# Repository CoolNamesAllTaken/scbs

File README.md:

# scbs
Single Cell Battery Simulator for testing a BMS.

# CELLSIM 4S

Cellsim 4S is a low-current battery pack simulator that simulates four battery cells in series. Each cell has a settable output voltage between 2.5-4.5V and a readable output current. Communication is done over a 9600 baud UART link using a custom serial protocol.

[DATASHEET](word/datasheet_cellsim_4s-1.0.0.pdf)

# SCBS Pico

SCBS Pico is a single battery cell simulator that can be daisy chained with other devices of the same type in order to build a full simulated battery pack. It is the basic building block of the CELLSIM 4S.

[DATASHEET](word/datasheet_scbs_pico.pdf)

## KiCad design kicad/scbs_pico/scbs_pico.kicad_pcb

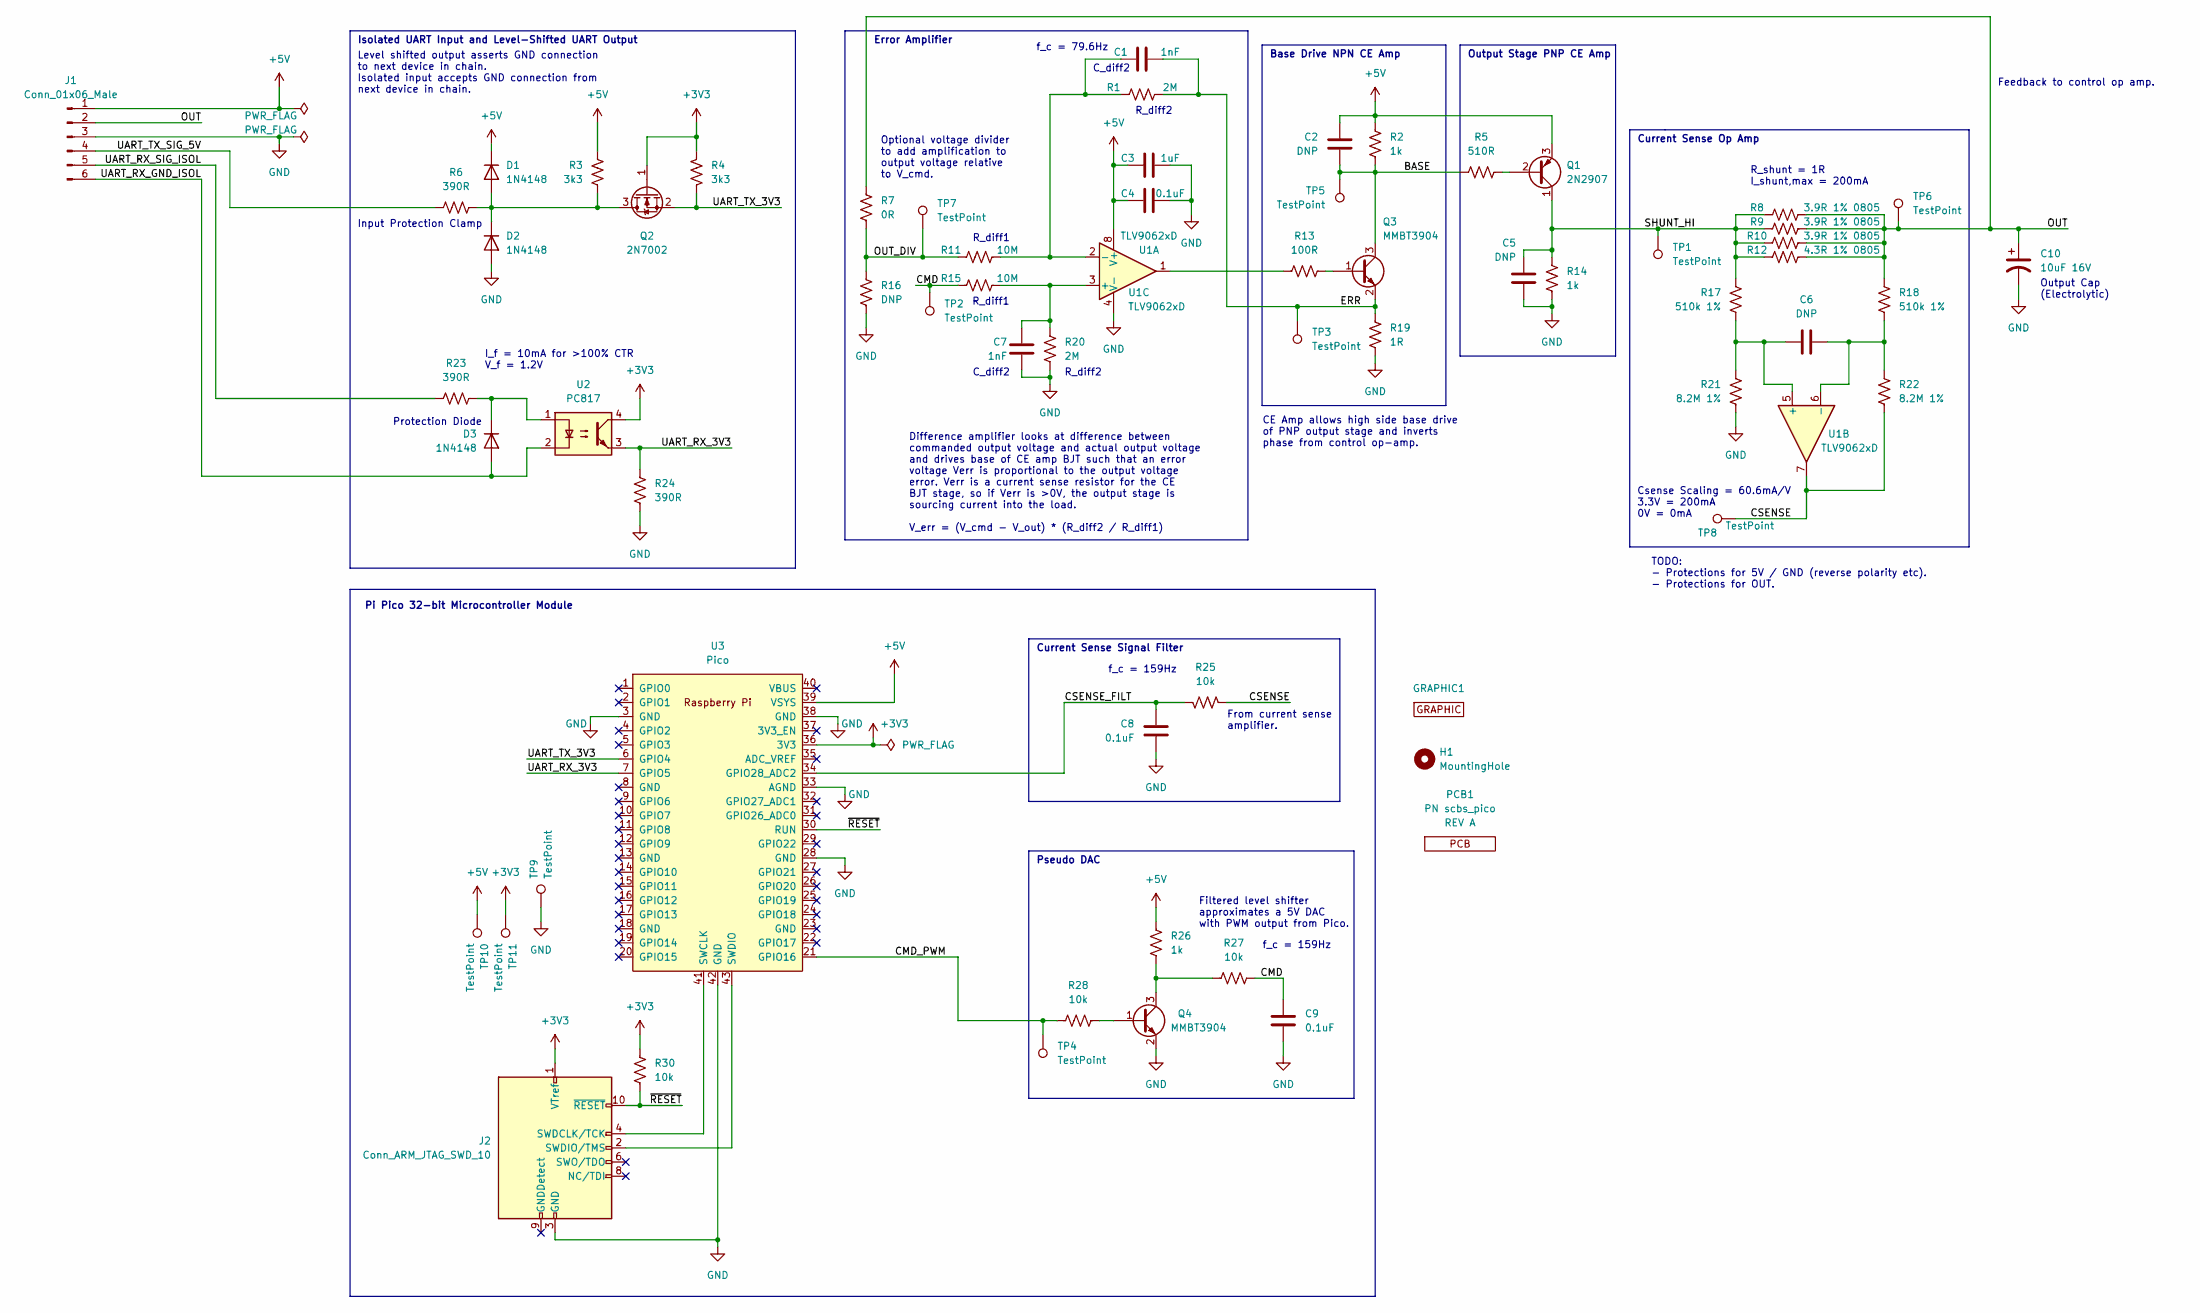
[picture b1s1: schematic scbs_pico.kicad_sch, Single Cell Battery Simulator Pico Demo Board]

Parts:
C1, C7: 1nF; C_0805_2012Metric
C2, C5, C6: DNP; C_0805_2012Metric
C3: 1uF; C_0805_2012Metric
C4, C8, C9: 0.1uF; C_0805_2012Metric
C10: 10uF 16V
D1, D2, D3: 1N4148; D_SOD-123; MPN 1N4148W-TP
GRAPHIC1: Graphic; bird_with_pants_small_flipped; MPN DNP
H1: MountingHole; MountingHole_3.2mm_M3; MPN DNP
J1: Conn_01x06_Male; PinHeader_1x06_P2.54mm_Horizontal; MPN PREC006SBAN-M71RC
J2: Conn_ARM_JTAG_SWD_10; PinHeader_2x05_P1.27mm_Vertical_SMD; MPN 4048
PCB1: PCB; PCB_PN_REV_small; MPN PN scbs_pico
Q1: 2N2907; TO-92; MPN PN2907ATF
Q2: 2N7002; SOT-23; MPN 2N7002
Q3, Q4: MMBT3904; SOT-23
R1, R20: 2M; R_0805_2012Metric
R2, R14, R26: 1k; R_0805_2012Metric
R3, R4: 3k3; R_0805_2012Metric
R5: 510R; R_0805_2012Metric
R6, R23, R24: 390R; R_0805_2012Metric
R7: 0R; R_0805_2012Metric
R8, R9, R10: 3.9R 1% 0805; R_0805_2012Metric
R11, R15: 10M; R_0805_2012Metric
R12: 4.3R 1% 0805; R_0805_2012Metric
R13: 100R; R_0805_2012Metric
R16: DNP; R_0805_2012Metric
R17, R18: 510k 1%; R_0805_2012Metric
R19: 1R; R_0805_2012Metric
R21, R22: 8.2M 1%; R_0805_2012Metric
R25, R27, R28, R30: 10k; R_0805_2012Metric
TP1, TP2, TP3, TP4, TP5, TP6, TP7, TP8, TP9, TP10, TP11: TestPoint; TestPoint_Pad_2.0x2.0mm
U1: TLV9062xD; SOIC-8_3.9x4.9mm_P1.27mm; MPN TLV9062IDR
U2: PC817; DIP-4_W7.62mm; MPN BPC-817S ( C BIN )
U3: Pico; RPi_Pico_SMD_TH; MPN SC0915

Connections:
+3V3: J2.1 (VTref), Q2.1 (G), R4.1, R30.1, TP11.1, U2.4, U3.36 (3V3)
+5V: C2.1, C3.1, C4.1, D1.1 (K), J1.1, Q1.3 (E), R2.1, R3.1, R26.1, TP10.1, U1.8 (V+), U3.39 (VSYS)
/BASE: C2.2, Q3.3 (C), R2.2, R5.1, TP5.1
/CMD: C9.1, R15.1, R27.2, TP2.1
/CMD_PWM: R28.1, TP4.1, U3.21 (GPIO16)
/CSENSE: R22.2, R25.1, TP8.1, U1.7
/CSENSE_FILT: C8.1, R25.2, U3.34 (GPIO28_ADC2)
/ERR: C1.2, Q3.2 (E), R1.2, R19.1, TP3.1
/OUT: C10.1, J1.2, R7.1, R8.2, R9.2, R10.2, R12.2, R18.1, TP6.1
/OUT_DIV: R7.2, R11.1, R16.1, TP7.1
/SHUNT_HI: C5.1, Q1.1 (C), R8.1, R9.1, R10.1, R12.1, R14.1, R17.1, TP1.1
/UART_RX_3V3: R24.1, U2.3, U3.7 (GPIO5)
/UART_RX_GND_ISOL: D3.2 (A), J1.6, U2.2
/UART_RX_SIG_ISOL: J1.5, R23.1
/UART_TX_3V3: Q2.2 (S), R4.2, U3.6 (GPIO4)
/UART_TX_SIG_5V: J1.4, R6.1
/~RESET: J2.10 (~RESET), R30.2, U3.30 (RUN)
GND: C3.2, C4.2, C5.2, C7.2, C8.2, C9.2, C10.2, D2.2 (A), J1.3, J2.3 (GND), J2.5 (GND), Q4.2 (E), R14.2, R16.2, R19.2, R20.2, R21.2, R24.2, TP9.1, U1.4 (V-), U3.3 (GND), U3.28 (GND), U3.33 (AGND), U3.38 (GND), U3.42 (GND)
unnamed: C1.1, R1.1, R11.2, U1.2 (-)
unnamed: C6.1, R17.2, R21.1, U1.5 (+)
unnamed: C6.2, R18.2, R22.1, U1.6 (-)
unnamed: C7.1, R15.2, R20.1, U1.3 (+)
unnamed: D1.2 (A), D2.1 (K), Q2.3 (D), R3.2, R6.2
unnamed: D3.1 (K), R23.2, U2.1
unnamed: J2.2 (SWDIO/TMS), U3.43 (SWDIO)
unnamed: J2.4 (SWDCLK/TCK), U3.41 (SWCLK)
unnamed: Q1.2 (B), R5.2
unnamed: Q3.1 (B), R13.2
unnamed: Q4.1 (B), R28.2
unnamed: Q4.3 (C), R26.2, R27.1
unnamed: R13.1, U1.1

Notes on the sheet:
R_diff1
Input Protection Clamp
Difference amplifier looks at difference between commanded output voltage and actual output voltage and drives base of CE amp BJT such that an error voltage Verr is proportional to the output voltage error. Verr is a current sense resistor for the CE BJT stage, so if Verr is >0V, the output stage i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
Protection Diode
Error Amplifier
Pseudo DAC
f_c = 79.6Hz
f_c = 159Hz
Csense Scaling = 60.6mA/V 3.3V = 200mA 0V = 0mA
Current Sense Op Amp
C_diff2
Feedback to control op amp.
Isolated UART Input and Level-Shifted UART Output
Pi Pico 32-bit Microcontroller Module
Optional voltage divider to add amplification to output voltage relative to V_cmd.
Output Stage PNP CE Amp
R_diff2
From current sense amplifier.
CE Amp allows high side base drive of PNP output stage and inverts phase from control op-amp.
Filtered level shifter approximates a 5V DAC with PWM output from Pico.
TODO: - Protections for 5V / GND (reverse polarity etc). - Protections for OUT.
Base Drive NPN CE Amp
R_shunt = 1R I_shunt,max = 200mA
Output Cap (Electrolytic)
I_f = 10mA for >100% CTR V_f = 1.2V
Current Sense Signal Filter
Level shifted output asserts GND connection to next device in chain. Isolated input accepts GND connection from next device in chain.

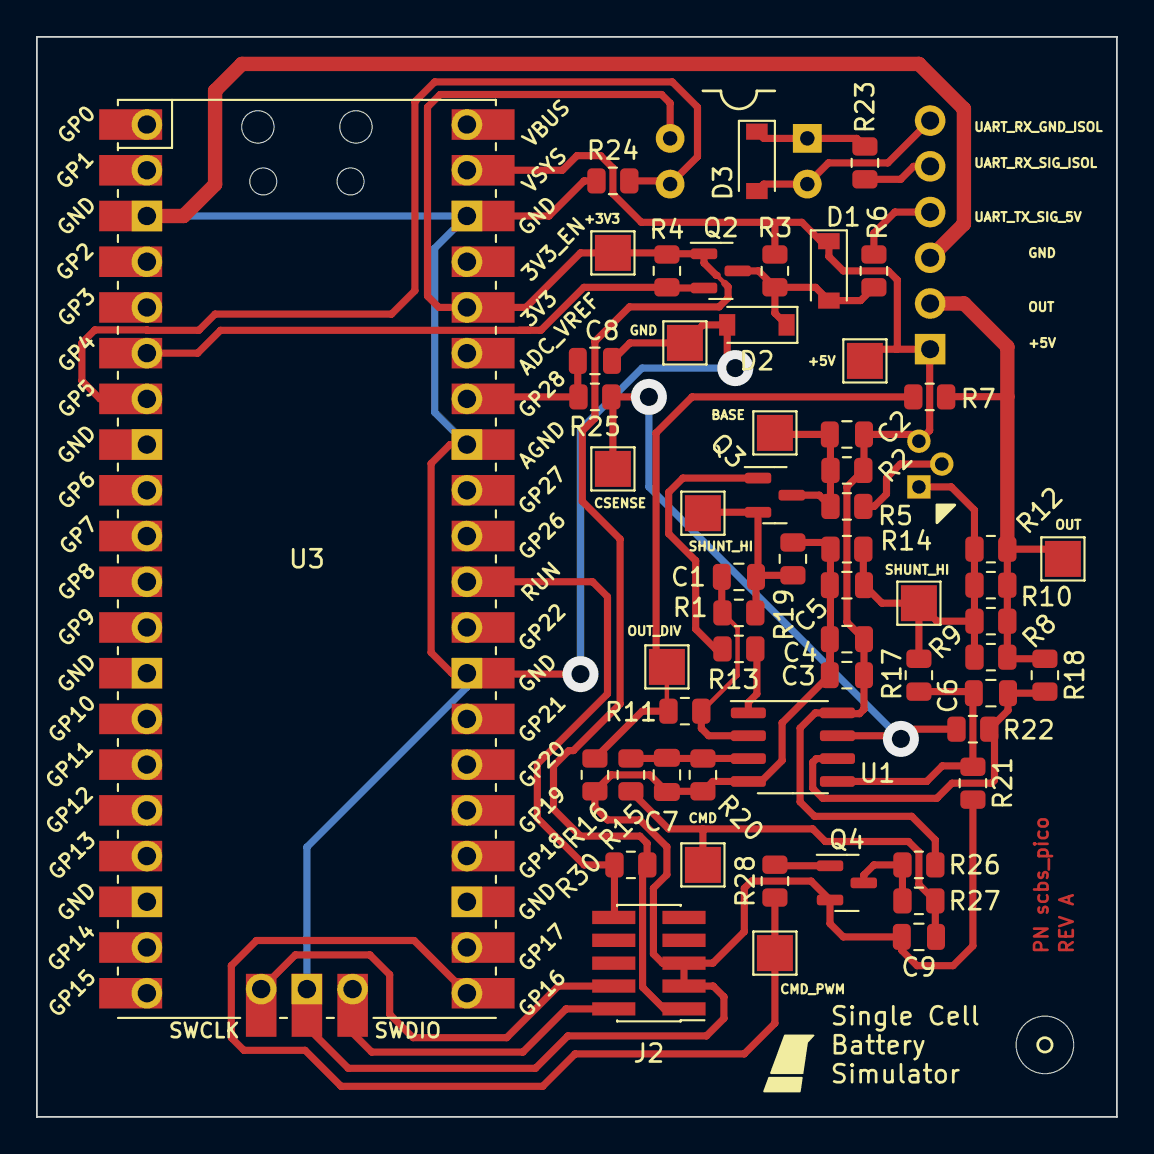
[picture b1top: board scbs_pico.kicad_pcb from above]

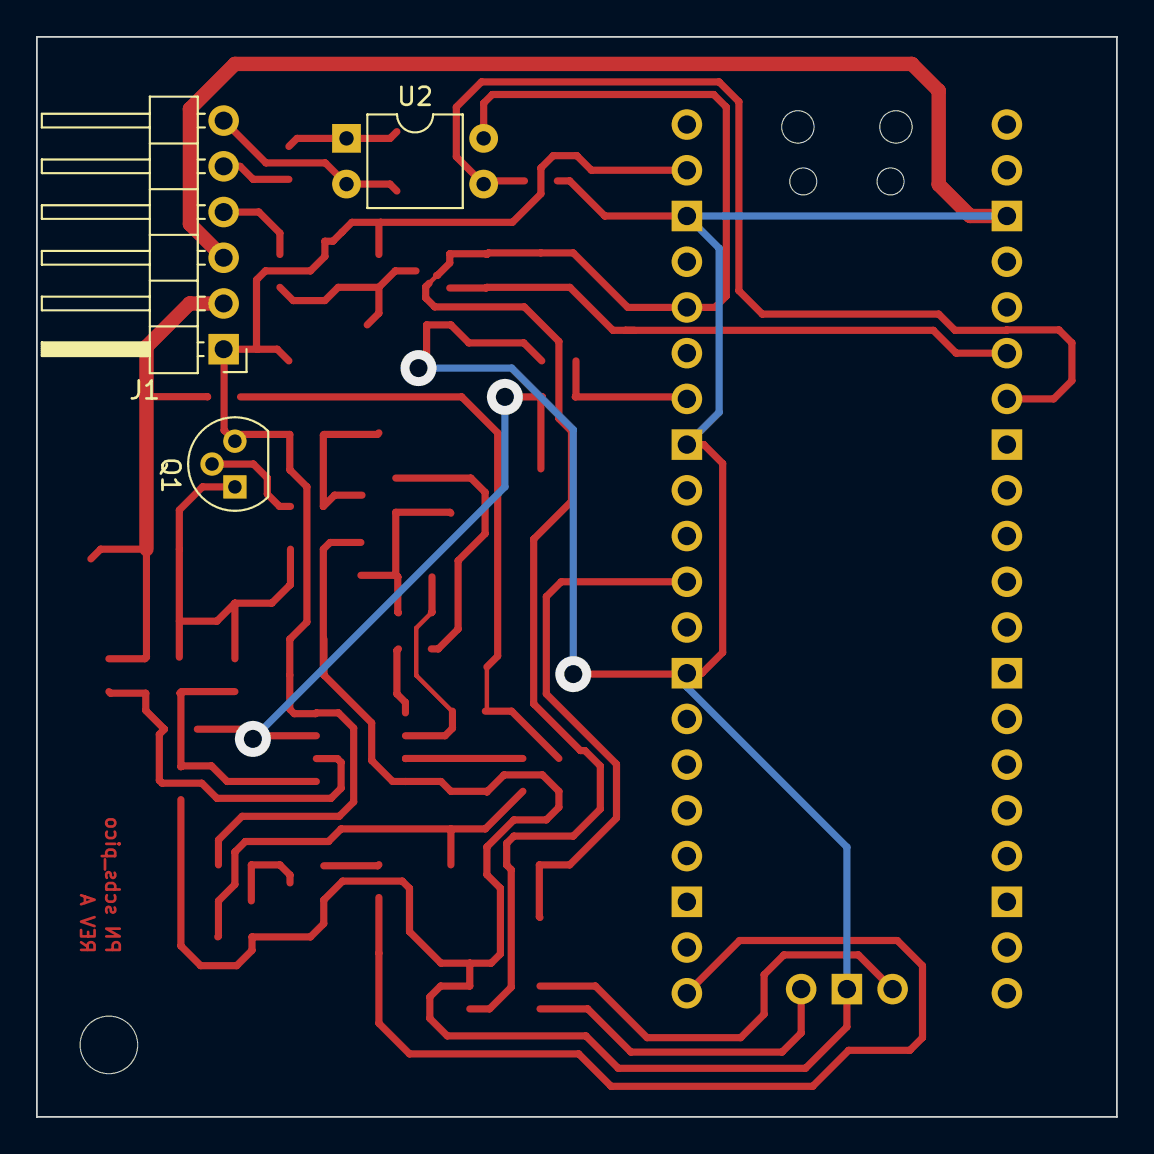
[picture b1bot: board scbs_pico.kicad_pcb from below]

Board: 2 copper layers, 60.0 x 60.0 mm, 64 parts (3 on the bottom side), 31 nets.

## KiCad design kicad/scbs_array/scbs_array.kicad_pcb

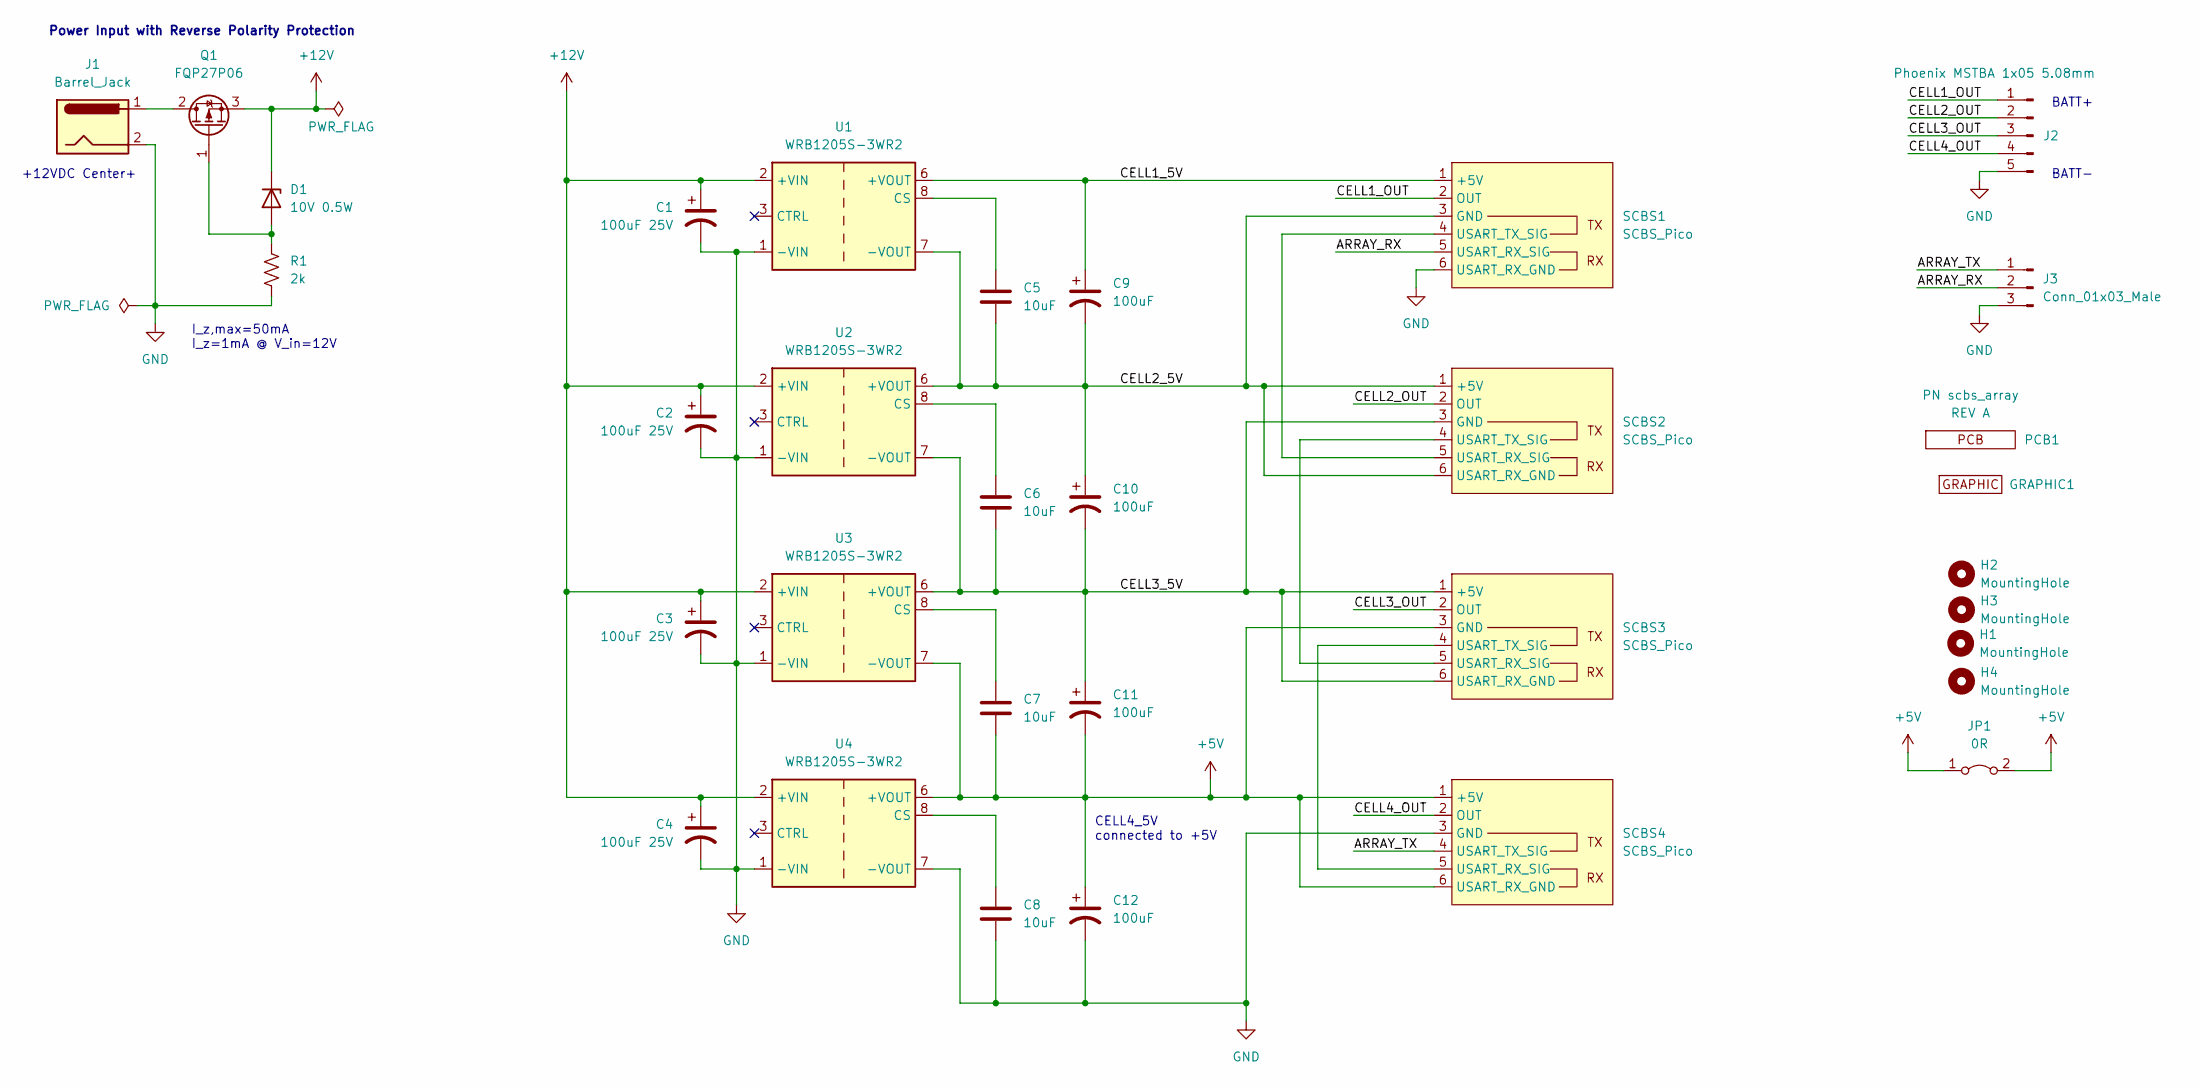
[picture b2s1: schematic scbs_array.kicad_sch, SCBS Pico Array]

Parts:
C1, C2, C3, C4: 100uF 25V; CP_Radial_D5.0mm_P2.50mm
C5, C6, C7, C8: 10uF; C_0805_2012Metric
C9, C10, C11, C12: 100uF; CP_Radial_D5.0mm_P2.50mm
D1: 10V 0.5W; D_MELF
GRAPHIC1: Graphic; bird_with_pants_small_flipped
H1, H2, H3, H4: MountingHole; MountingHole_3.2mm_M3
J1: Barrel_Jack; SOFNG_DC005-T20; MPN DC005-T20
J2: Phoenix MSTBA 1x05 5.08mm; PhoenixContact_MSTBA_2,5_5-G-5,08_1x05_P5.08mm_Horizontal
J3: Conn_01x03_Male; PinHeader_1x03_P2.54mm_Horizontal
JP1: 0R; R_0805_2012Metric
PCB1: PCB; PCB_PN_REV; MPN PN scbs_array
Q1: FQP27P06; TO-220-3_Horizontal_TabDown; MPN FQP27P06
R1: 2k; R_0805_2012Metric
SCBS1, SCBS2, SCBS3, SCBS4: SCBS_Pico
U1, U2, U3, U4: WRB1205S-3WR2; Converter_DCDC_TRACO_TMR-xxxx_THT

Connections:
+5V: C7.2, C11.2, C12.1, JP1.1 (A), JP1.2 (B), SCBS3.3 (GND), SCBS4.1 (+5V), SCBS4.6 (USART_RX_GND), U3.7 (-VOUT), U4.6 (+VOUT)
+12V: C1.1, C2.1, C3.1, C4.1, D1.1 (K), Q1.3 (S), U1.2 (+VIN), U2.2 (+VIN), U3.2 (+VIN), U4.2 (+VIN)
/ARRAY_RX: J3.2, SCBS1.5 (USART_RX_SIG)
/ARRAY_TX: J3.1, SCBS4.4 (USART_TX_SIG)
/CELL1_5V: C9.1, SCBS1.1 (+5V), U1.6 (+VOUT)
/CELL1_OUT: J2.1, SCBS1.2 (OUT)
/CELL2_5V: C5.2, C9.2, C10.1, SCBS1.3 (GND), SCBS2.1 (+5V), SCBS2.6 (USART_RX_GND), U1.7 (-VOUT), U2.6 (+VOUT)
/CELL2_OUT: J2.2, SCBS2.2 (OUT)
/CELL3_5V: C6.2, C10.2, C11.1, SCBS2.3 (GND), SCBS3.1 (+5V), SCBS3.6 (USART_RX_GND), U2.7 (-VOUT), U3.6 (+VOUT)
/CELL3_OUT: J2.3, SCBS3.2 (OUT)
/CELL4_OUT: J2.4, SCBS4.2 (OUT)
GND: C1.2, C2.2, C3.2, C4.2, C8.2, C12.2, J1.2, J2.5, J3.3, R1.2, SCBS1.6 (USART_RX_GND), SCBS4.3 (GND), U1.1 (-VIN), U2.1 (-VIN), U3.1 (-VIN), U4.1 (-VIN), U4.7 (-VOUT)
unnamed: C5.1, U1.8 (CS)
unnamed: C6.1, U2.8 (CS)
unnamed: C7.1, U3.8 (CS)
unnamed: C8.1, U4.8 (CS)
unnamed: D1.2 (A), Q1.1 (G), R1.1
unnamed: J1.1, Q1.2 (D)
unnamed: SCBS1.4 (USART_TX_SIG), SCBS2.5 (USART_RX_SIG)
unnamed: SCBS2.4 (USART_TX_SIG), SCBS3.5 (USART_RX_SIG)
unnamed: SCBS3.4 (USART_TX_SIG), SCBS4.5 (USART_RX_SIG)

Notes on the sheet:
+12VDC Center+
CELL4_5V connected to +5V
I_z,max=50mA I_z=1mA @ V_in=12V
Power Input with Reverse Polarity Protection
BATT-
BATT+

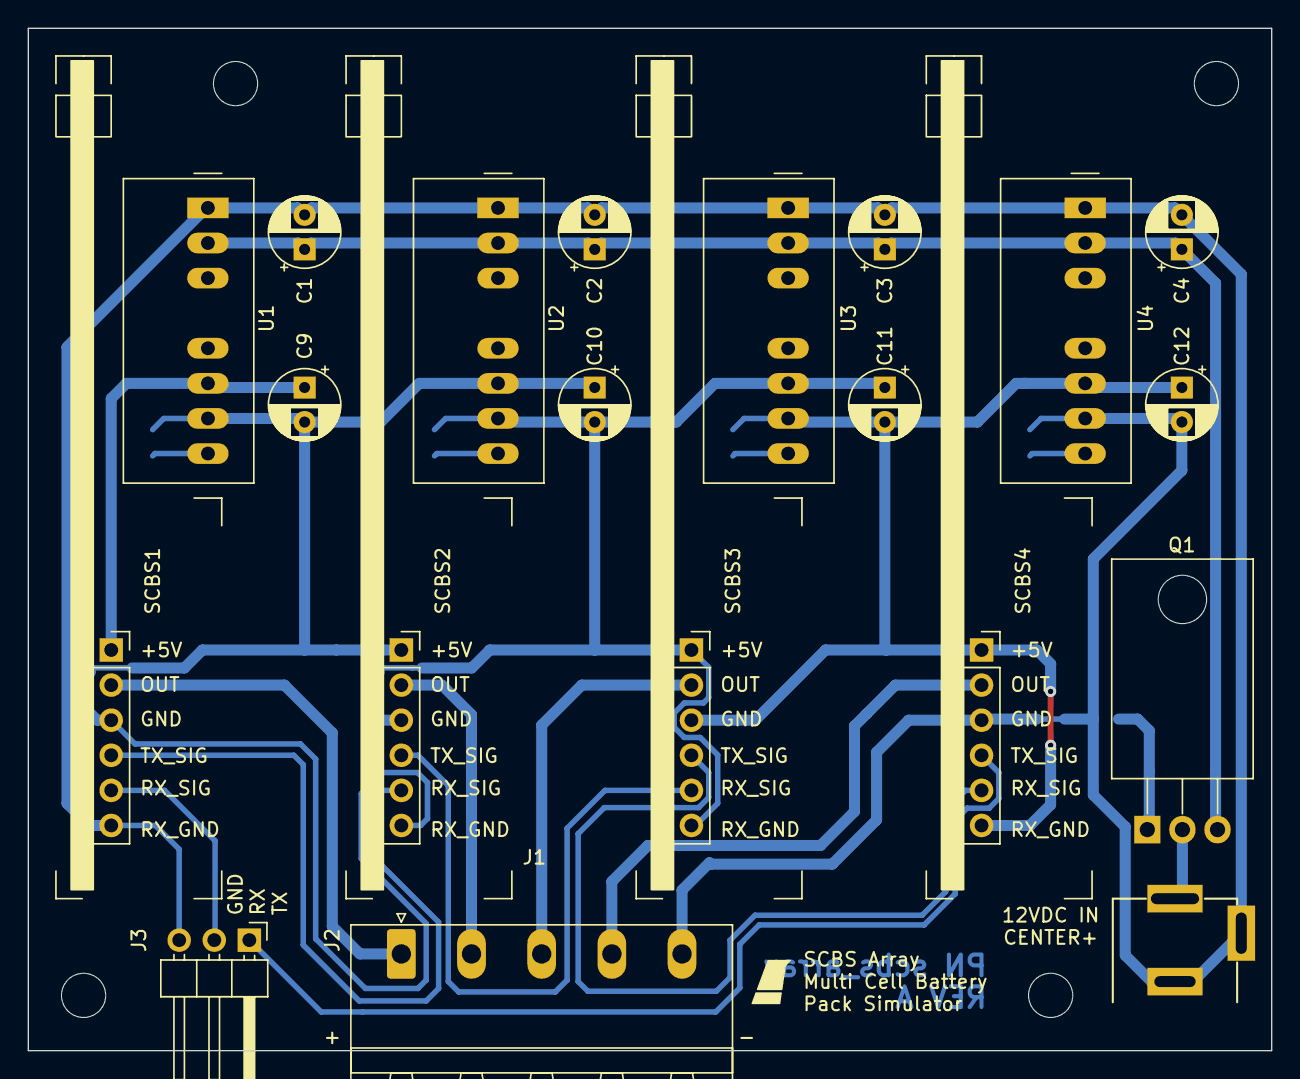
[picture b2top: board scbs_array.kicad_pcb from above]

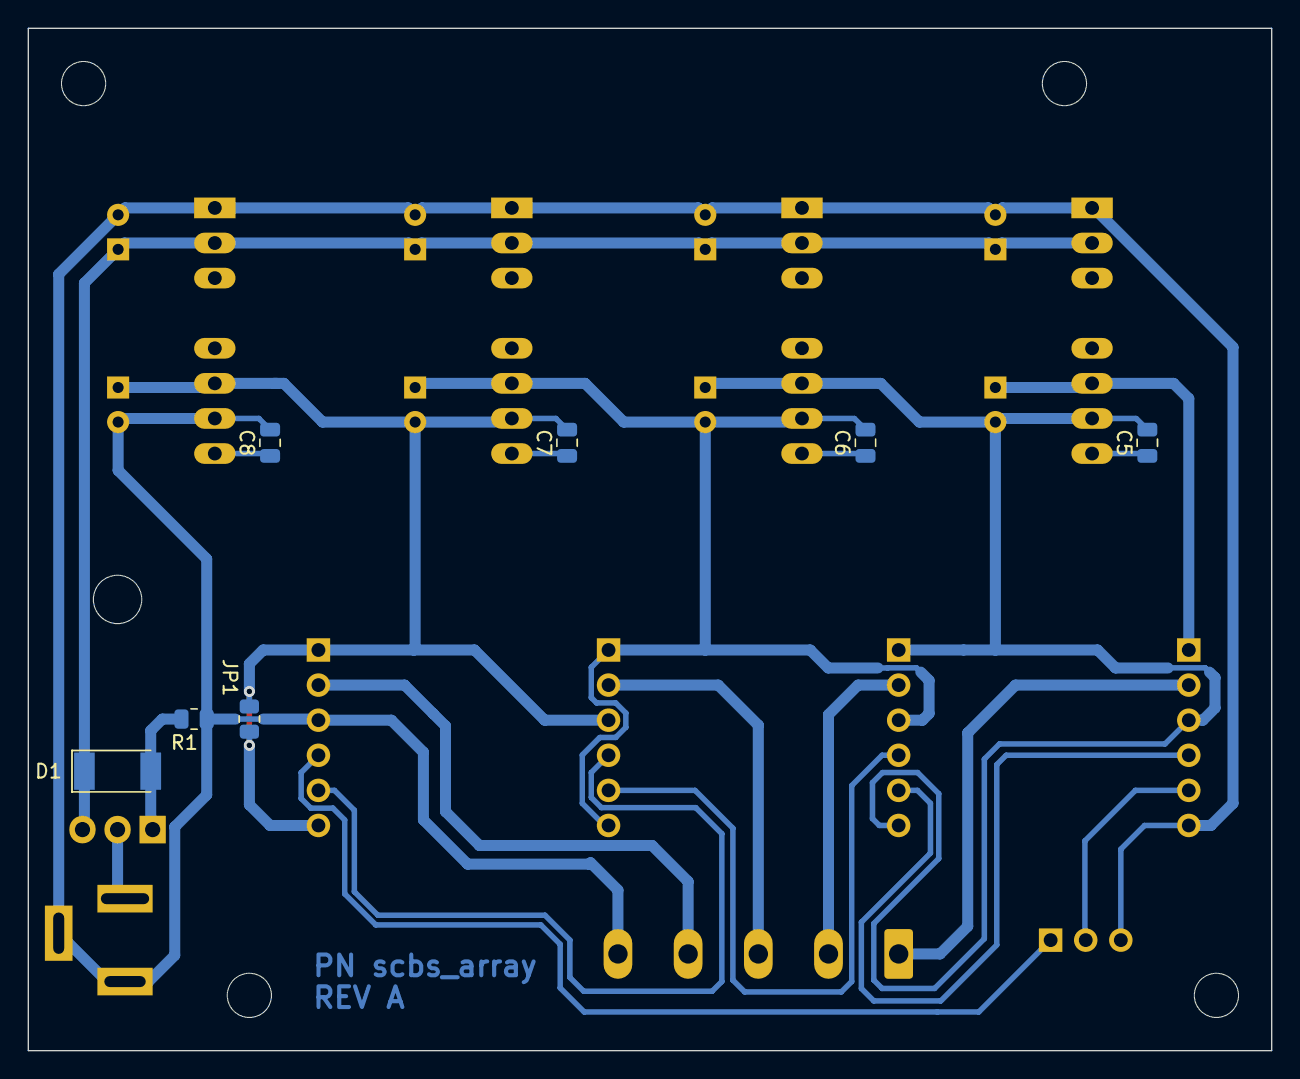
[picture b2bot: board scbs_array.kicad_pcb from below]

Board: 2 copper layers, 90.0 x 74.0 mm, 33 parts (8 on the bottom side), 21 nets.

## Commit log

2022-11-06 Demo board v0.1
2022-11-08 scbs_pico hardware Rev A, initial firmware
2022-11-12 Saving progress of unsuccessful mock attempt
2022-11-12 Add unit tested MRD packet type
2022-11-12 Working SCBS multi-read packets on device
2022-11-15 Add calibrated output voltage setting
    * Python script serial utility for sending DIS, MWR, MRD commands to
    device.
    * Three-coefficient polynomial calibration implemented in firmware for
    closer matching of output voltage (looks pretty darn good)! Makes up
    for the crappiness / non-linearity of the PWM pseudo-DAC driving a
    load without a buffer.
2022-11-25 Add SCBS array PCBA Rev A
    * Update design notebook.
    * Export some stuff for SCBS Pico.
    * Create SCBS Array motherboard.
2022-11-26 Make enclosure CAD
2022-12-04 SCBS Array design, add single cell packets
2022-12-09 Add CELLSIM 4S documentation
